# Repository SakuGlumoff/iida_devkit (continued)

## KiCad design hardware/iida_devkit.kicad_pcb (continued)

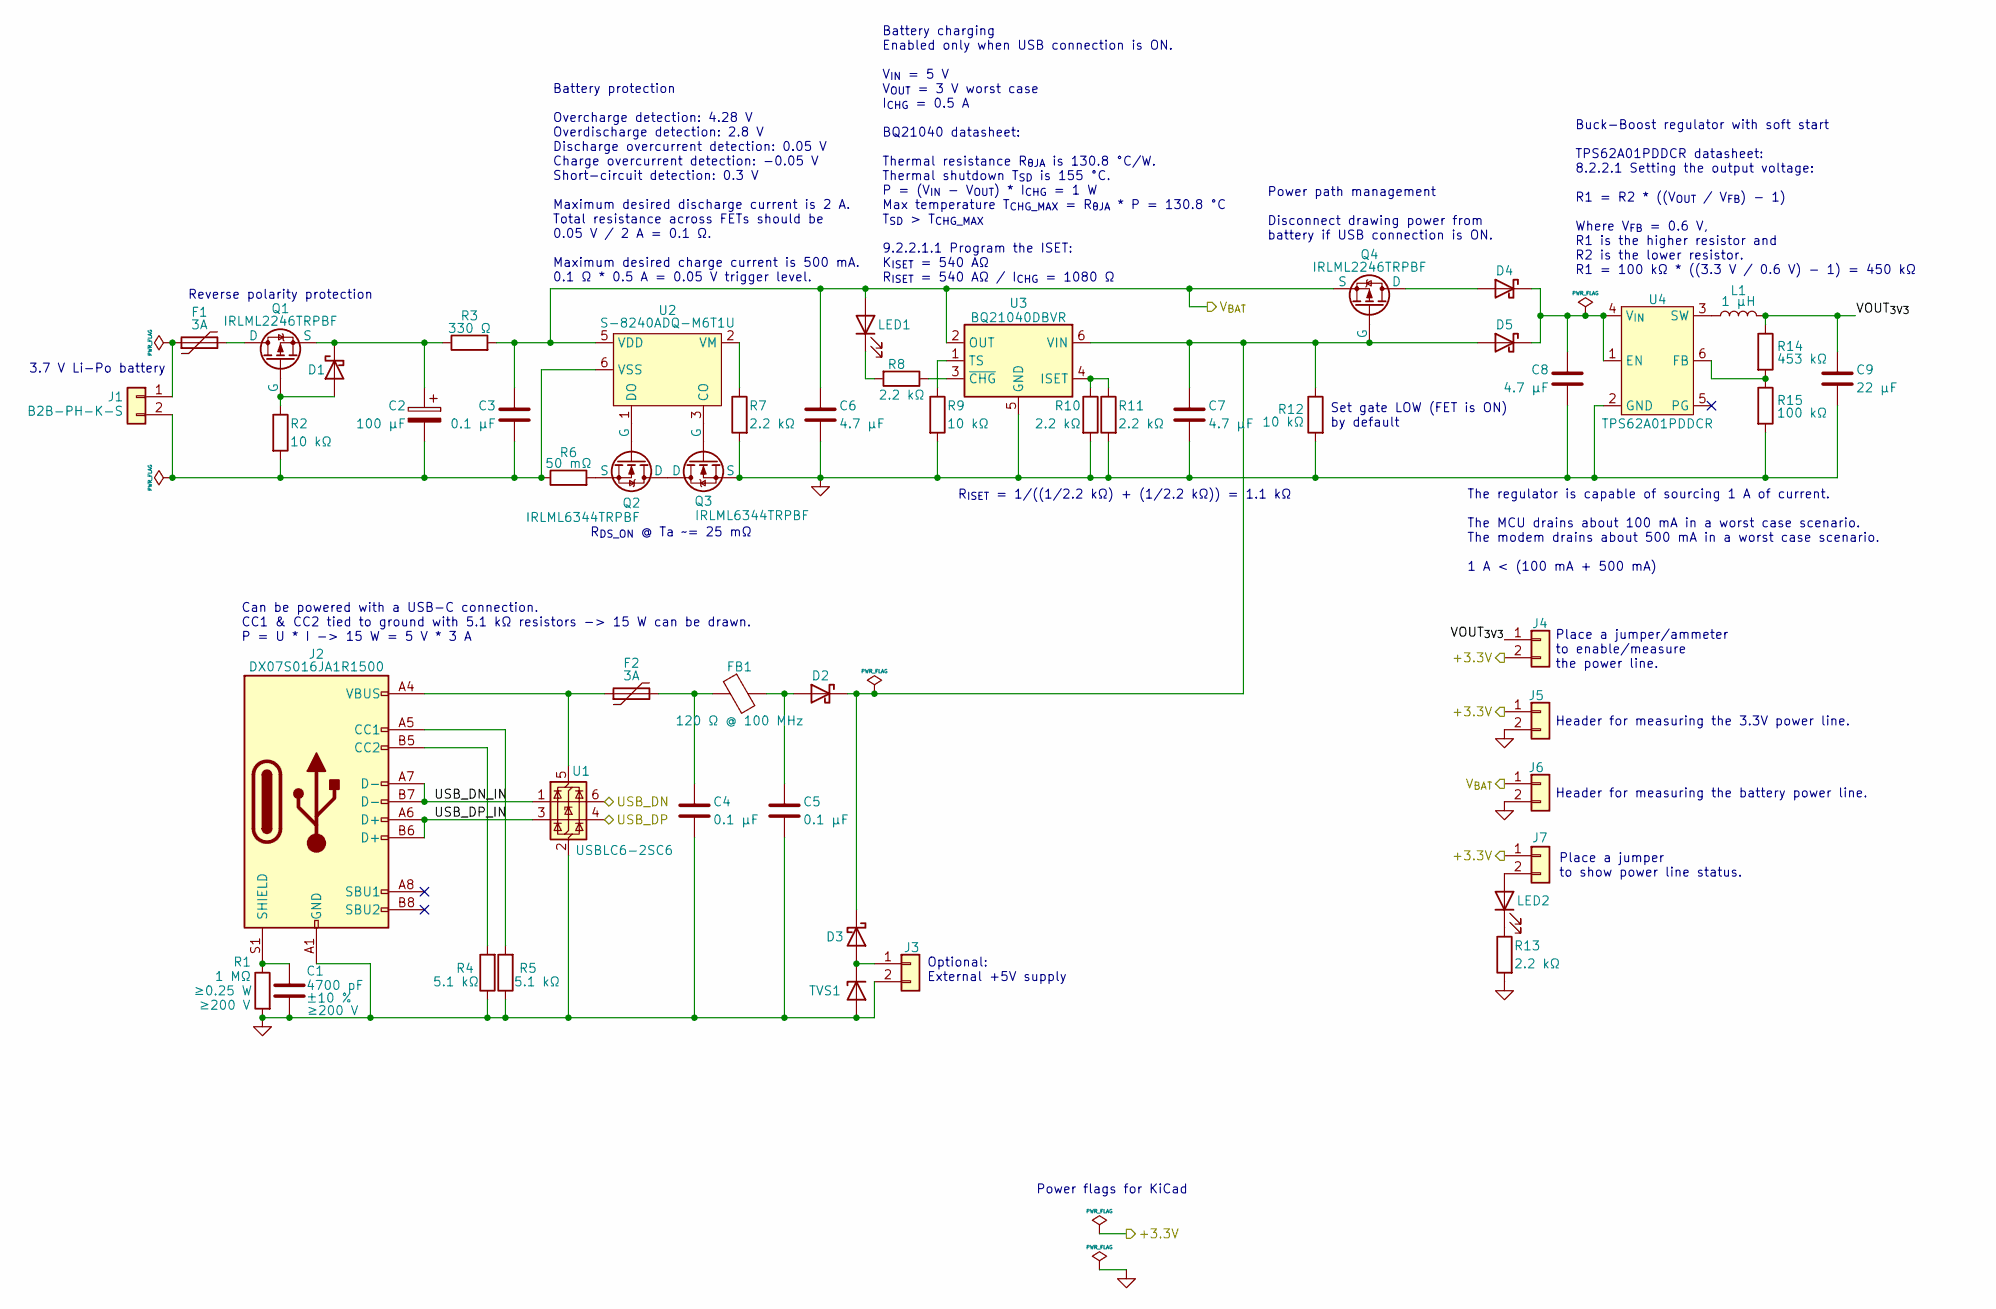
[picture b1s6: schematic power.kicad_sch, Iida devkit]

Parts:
C1: 4700 pF; C_0805_2012Metric_Pad1.18x1.45mm_HandSolder; Voltage rating ≥200 V; Tolerance ±10 %; Manufacturer Part Number 885342207009; Digi-Key Part Number 732-12165-1-ND
C2: 100 µF; CP_Elec_5x5.3; Manufacturer Part Number 865080142007; Digi-Key Part Number 732-8472-1-ND
C3, C4, C5: 0.1 µF; C_0603_1608Metric_Pad1.08x0.95mm_HandSolder; Manufacturer Part Number 885012206071; Digi-Key Part Number 732-7989-1-ND
C6, C7, C8: 4.7 µF; C_0805_2012Metric_Pad1.18x1.45mm_HandSolder; Manufacturer Part Number 885012107013; Digi-Key Part Number 732-7623-1-ND
C9: 22 µF; C_0805_2012Metric_Pad1.18x1.45mm_HandSolder; Manufacturer Part Number 885012107005; Digi-Key Part Number 732-7616-1-ND
D1, D2, D3, D4, D5: BAT60AE6327HTSA1; D_SOD-323_HandSoldering; Manufacturer Part Number BAT60AE6327HTSA1; Digi-Key Part Number BAT60AE6327HTSA1CT-ND
F1, F2: 3A; R_0805_2012Metric_Pad1.20x1.40mm_HandSolder; Manufacturer Part Number PTSLR08056V150; Digi-Key Part Number 283-PTSLR08056V150CT-ND
FB1: 120 Ω @ 100 MHz; R_0603_1608Metric_Pad0.98x0.95mm_HandSolder; Manufacturer Part Number BLM18KG121TN1D; Digi-Key Part Number 490-5254-1-ND
J1: B2B-PH-K-S; JST_PH_B2B-PH-K_1x02_P2.00mm_Vertical; Manufacturer Part Number B2B-PH-K-S; Digi-Key Part Number 455-1704-ND
J2: DX07S016JA1R1500; Manufacturer Part Number DX07S016JA1R1500; Digi-Key Part Number 670-DX07S016JA1R1500CT-ND
J3, J4, J5, J6, J7: PRPC001DAAN-RC; PinHeader_1x02_P2.54mm_Vertical; Manufacturer Part Number PRPC001DAAN-RC; Digi-Key Part Number S2011EC-01-ND
L1: 1 µH; L_1008_2520Metric_Pad1.43x2.20mm_HandSolder; Manufacturer Part Number DFE252012F-1R0M=P2; Digi-Key Part Number 490-13053-1-ND
LED1, LED2: 150141YS73100; LED_PLCC_2835_Handsoldering; Manufacturer Part Number 150141YS73100; Digi-Key Part Number 732-5004-1-ND
Q1, Q4: IRLML2246TRPBF; SC-59_Handsoldering; Manufacturer Part Number IRLML2246TRPBF; Digi-Key Part Number IRLML2246TRPBFCT-ND
Q2, Q3: IRLML6344TRPBF; SC-59_Handsoldering; Manufacturer Part Number IRLML6344TRPBF; Digi-Key Part Number IRLML6344TRPBFCT-ND
R1: 1 MΩ; R_1206_3216Metric_Pad1.30x1.75mm_HandSolder; Power rating ≥0.25 W; Working voltage ≥200 V; Manufacturer Part Number 560112132011; Digi-Key Part Number 732-560112132011CT-ND
R2, R9, R12: 10 kΩ; R_0603_1608Metric_Pad0.98x0.95mm_HandSolder; Manufacturer Part Number 560112116005; Digi-Key Part Number 732-560112116005CT-ND
R3: 330 Ω; R_0603_1608Metric_Pad0.98x0.95mm_HandSolder; Manufacturer Part Number 560112116020; Digi-Key Part Number 732-560112116020CT-ND
R4, R5: 5.1 kΩ; R_0805_2012Metric_Pad1.20x1.40mm_HandSolder; Manufacturer Part Number 560112120019; Digi-Key Part Number 732-560112120019CT-ND
R6: 50 mΩ; R_0603_1608Metric_Pad0.98x0.95mm_HandSolder; Manufacturer Part Number ERJ-3BWFR050V; Digi-Key Part Number P17472CT-ND
R7, R8, R10, R11, R13: 2.2 kΩ; R_0603_1608Metric_Pad0.98x0.95mm_HandSolder; Manufacturer Part Number 560112116098; Digi-Key Part Number 732-560112116098CT-ND
R14: 453 kΩ; R_0603_1608Metric_Pad0.98x0.95mm_HandSolder; Manufacturer Part Number SDR03EZPF4533; Digi-Key Part Number 846-SDR03EZPF4533CT-ND
R15: 100 kΩ; R_0603_1608Metric_Pad0.98x0.95mm_HandSolder; Manufacturer Part Number 560112116004; Digi-Key Part Number 732-560112116004CT-ND
TVS1: SMAJ6.0CA; D_SMA_Handsoldering; Manufacturer Part Number SMAJ6.0CA; Digi-Key Part Number 732-SMAJ6.0CACT-ND
U1: USBLC6-2SC6; SOT-23-6_Handsoldering; Manufacturer Part Number USBLC6-2SC6; Digi-Key Part Number 497-5235-1-ND
U2: S-8240ADQ-M6T1U; SOT-23-6_Handsoldering; Manufacturer Part Number S-8240ADQ-M6T1U; Digi-Key Part Number 1662-S-8240ADQ-M6T1UCT-ND
U3: BQ21040DBVR; SOT-23-6_Handsoldering; Manufacturer Part Number BQ21040DBVR; Digi-Key Part Number 296-47315-1-ND
U4: TPS62A01PDDCR; SOT-23-6_Handsoldering; Manufacturer Part Number TPS62A01PDDCR; Digi-Key Part Number 296-TPS62A01PDDCRCT-ND

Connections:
+3.3V: J4.2, J5.1, J7.1; also elsewhere on the board
+VBAT: C3.1, C6.1, J6.1, LED1.2 (A), Q4.3 (S), R3.2, U2.5 (VDD), U3.2 (OUT); also elsewhere on the board
/MCU/USB_DN: U1.6 (I/O1); also elsewhere on the board
/MCU/USB_DP: U1.4 (I/O2); also elsewhere on the board
/Power/USB_DN_IN: J2.A7 (D-), J2.B7 (D-), U1.1 (I/O1)
/Power/USB_DP_IN: J2.A6 (D+), J2.B6 (D+), U1.3 (I/O2)
/Power/VOUT_{3V3}: C9.1, J4.1, L1.2, R14.1
GND: C1.2, C4.2, C5.2, C6.2, C7.2, C8.2, C9.2, J2.A1 (GND), J2.A12 (GND), J2.B1 (GND), J2.B12 (GND), J3.2, J5.2, J6.2, Q3.3 (S), R1.2, R4.1, R5.1, R7.2, R9.2, R10.2, R11.2, R12.2, R13.2, R15.2, TVS1.2 (A), U1.2 (GND), U3.5 (GND), U4.2 (GND); also elsewhere on the board
unnamed: C4.1, F2.2, FB1.1
unnamed: D1.2 (A), Q1.2 (G), R2.1
unnamed: C2.1, D1.1 (K), Q1.3 (S), R3.1
unnamed: C5.1, D2.2 (A), FB1.2
unnamed: C7.1, D2.1 (K), D3.1 (K), D5.2 (A), Q4.2 (G), R12.1, U3.6 (VIN)
unnamed: D3.2 (A), J3.1, TVS1.1 (K)
unnamed: D4.2 (A), Q4.1 (D)
unnamed: C8.1, D4.1 (K), D5.1 (K), U4.1 (EN), U4.4 (V_{IN})
unnamed: F1.1, J1.1
unnamed: C2.2, C3.2, J1.2, R2.2, R6.1, U2.6 (VSS)
unnamed: J2.A5 (CC1), R5.2
unnamed: J2.B5 (CC2), R4.2
unnamed: C1.1, J2.S1 (SHIELD), R1.1
unnamed: J7.2, LED2.2 (A)
unnamed: LED1.1 (K), R8.2
unnamed: LED2.1 (K), R13.1
unnamed: F1.2, Q1.1 (D)
unnamed: Q2.1 (D), Q3.1 (D)
unnamed: Q2.2 (G), U2.1 (DO)
unnamed: Q2.3 (S), R6.2
unnamed: Q3.2 (G), U2.3 (CO)
unnamed: F2.1, J2.A4 (VBUS), J2.A9 (VBUS), J2.B4 (VBUS), J2.B9 (VBUS), U1.5 (VBUS)
unnamed: R7.1, U2.2 (VM)
unnamed: R10.1, R11.1, U3.4 (ISET)
unnamed: R9.1, U3.1 (TS)
unnamed: R8.1, U3.3 (~CHG)
unnamed: R14.2, R15.1, U4.6 (FB)
unnamed: L1.1, U4.3 (SW)

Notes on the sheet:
R_{ISET} = 1/((1/2.2 kΩ) + (1/2.2 kΩ)) = 1.1 kΩ
Can be powered with a USB-C connection. CC1 & CC2 tied to ground with 5.1 kΩ resistors -> 15 W can be drawn. P = U * I -> 15 W = 5 V * 3 A
R_{DS_ON} @ Ta ~= 25 mΩ
3.7 V Li-Po battery
Reverse polarity protection
Set gate LOW (FET is ON) by default
Buck-Boost regulator with soft start TPS62A01PDDCR datasheet: 8.2.2.1 Setting the output voltage: R1 = R2 * ((V_{OUT} / V_{FB}) - 1) Where V_{FB} = 0.6 V, R1 is the higher resistor and R2 is the lower resistor. R1 = 100 kΩ * ((3.3 V / 0.6 V) - 1) = 450 kΩ
Power path management Disconnect drawing power from battery if USB connection is ON.
Optional: External +5V supply
Power flags for KiCad
Place a jumper to show power line status.
Header for measuring the battery power line.
Battery protection Overcharge detection: 4.28 V Overdischarge detection: 2.8 V Discharge overcurrent detection: 0.05 V Charge overcurrent detection: -0.05 V Short-circuit detection: 0.3 V Maximum desired discharge current is 2 A. Total resistance across FETs should be 0.05 V / 2 A = 0.1 Ω. Maximum 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
Battery charging Enabled only when USB connection is ON. V_{IN} = 5 V V_{OUT} = 3 V worst case I_{CHG} = 0.5 A BQ21040 datasheet: Thermal resistance R_{θJA} is 130.8 °C/W. Thermal shutdown T_{SD} is 155 °C. P = (V_{IN} - V_{OUT}) * I_{CHG} = 1 W Max temperature T_{CHG_MAX} = R_{θJA} * P = 130.8 °C 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
Place a jumper/ammeter to enable/measure the power line.
Header for measuring the 3.3V power line.
The regulator is capable of sourcing 1 A of current. The MCU drains about 100 mA in a worst case scenario. The modem drains about 500 mA in a worst case scenario. 1 A < (100 mA + 500 mA)

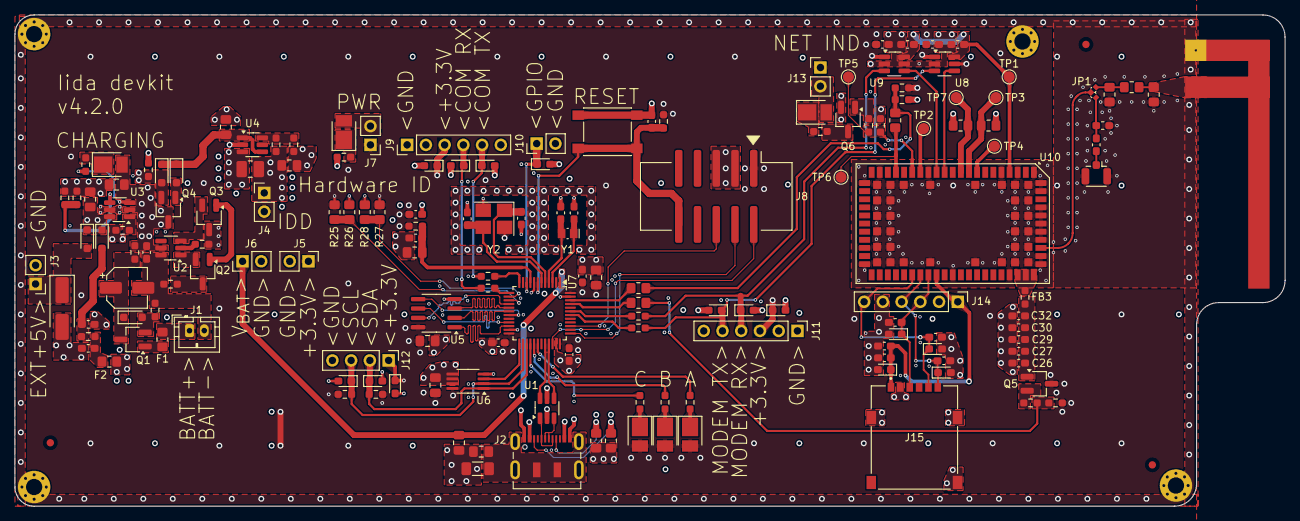
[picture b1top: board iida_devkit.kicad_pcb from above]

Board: 4 copper layers, 172.2 x 66.6 mm, 167 parts (0 on the bottom side), 100 nets.

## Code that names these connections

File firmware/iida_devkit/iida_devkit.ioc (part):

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Mcu.Name=STM32L552C(C-E)Tx
Mcu.Package=LQFP48
Mcu.UserName=STM32L552CETx
PA11.GPIOParameters=GPIO_Label
PA11.GPIO_Label=USB_DN
PA11.Mode=Device
PA11.Signal=USB_DM
PA12.Mode=Device
PA12.Signal=USB_DP
PA13\ (JTMS/SWDIO).GPIOParameters=GPIO_Label
PA13\ (JTMS/SWDIO).GPIO_Label=SWDIO
PA13\ (JTMS/SWDIO).Mode=Trace_Asynchronous_SW
PA13\ (JTMS/SWDIO).Signal=DEBUG_JTMS-SWDIO
PA14\ (JTCK/SWCLK).GPIOParameters=GPIO_Label
PA14\ (JTCK/SWCLK).GPIO_Label=SWCLK
PA14\ (JTCK/SWCLK).Mode=Trace_Asynchronous_SW
PA14\ (JTCK/SWCLK).Signal=DEBUG_JTCK-SWCLK
PA2.GPIOParameters=GPIO_Label
PA2.GPIO_Label=COM_UART_TX
PA2.Mode=Asynchronous
PA2.Signal=USART2_TX
PA3.GPIOParameters=GPIO_Label
PA3.GPIO_Label=COM_UART_RX
PA3.Mode=Asynchronous
PA3.Signal=USART2_RX
PA4.GPIOParameters=GPIO_Label
PA4.GPIO_Label=HWID_1
PA4.Signal=GPIO_Input
PA5.GPIOParameters=GPIO_Label
PA5.GPIO_Label=HWID_2
PA5.Signal=GPIO_Input
PA6.GPIOParameters=GPIO_Label
PA6.GPIO_Label=EXT_FLASH_IO3
PA6.Mode=quad_mode
PA6.Signal=OCTOSPI1_IO3
PA7.GPIOParameters=GPIO_Label
PA7.GPIO_Label=EXT_FLASH_IO2
PA7.Mode=quad_mode
PA7.Signal=OCTOSPI1_IO2
PA8.GPIOParameters=GPIO_Label
PA8.GPIO_Label=LED_B
PA8.Signal=GPIO_Output
PA9.GPIOParameters=GPIO_Label
PA9.GPIO_Label=LED_A
PA9.Signal=GPIO_Output
PB0.GPIOParameters=GPIO_Label
PB0.GPIO_Label=EXT_FLASH_IO1
PB0.Mode=quad_mode
PB0.Signal=OCTOSPI1_IO1
PB1.GPIOParameters=GPIO_Label
PB1.GPIO_Label=EXT_FLASH_IO0
PB1.Mode=quad_mode
PB1.Signal=OCTOSPI1_IO0
PB10.GPIOParameters=GPIO_Label
PB10.GPIO_Label=EXT_FLASH_CLK
PB10.Mode=quad_mode
PB10.Signal=OCTOSPI1_CLK
PB11.GPIOParameters=GPIO_Label
PB11.GPIO_Label=EXT_FLASH_NCS
PB11.Mode=quad_mode
PB11.Signal=OCTOSPI1_NCS
PB12.GPIOParameters=GPIO_Label
PB12.GPIO_Label=TEMP_ALERT
PB12.Signal=GPXTI12
PB13.GPIOParameters=GPIO_Label
PB13.GPIO_Label=I2C_SCL
PB13.Mode=I2C
PB13.Signal=I2C2_SCL
PB14.GPIOParameters=GPIO_Label
PB14.GPIO_Label=I2C_SDA
PB14.Mode=I2C
PB14.Signal=I2C2_SDA
PB15.GPIOParameters=GPIO_Label
PB15.GPIO_Label=LED_C
PB15.Signal=GPIO_Output
PB3\ (JTDO/TRACESWO).GPIOParameters=GPIO_Label
PB3\ (JTDO/TRACESWO).GPIO_Label=SWO
PB3\ (JTDO/TRACESWO).Mode=Trace_Asynchronous_SW
PB3\ (JTDO/TRACESWO).Signal=DEBUG_JTDO-SWO
PB6.GPIOParameters=GPIO_Label
PB6.GPIO_Label=MODEM_TX
PB6.Mode=Asynchronous
PB6.Signal=USART1_TX
PB7.GPIOParameters=GPIO_Label
PB7.GPIO_Label=MODEM_RX
PB7.Mode=Asynchronous
PB7.Signal=USART1_RX
PB8.GPIOParameters=GPIO_Label
PB8.GPIO_Label=MODEM_PWR_EN_N
PB8.Signal=GPIO_Output
PB9.GPIOParameters=GPIO_Label
PB9.GPIO_Label=MODEM_RESET_N
PB9.Signal=GPIO_Output
PC14-OSC32_IN\ (PC14).GPIOParameters=GPIO_Label
PC14-OSC32_IN\ (PC14).GPIO_Label=LSE_IN
PC14-OSC32_IN\ (PC14).Mode=LSE-External-Oscillator
PC14-OSC32_IN\ (PC14).Signal=RCC_OSC32_IN
PC15-OSC32_OUT\ (PC15).GPIOParameters=GPIO_Label
PC15-OSC32_OUT\ (PC15).GPIO_Label=LSE_OUT
PC15-OSC32_OUT\ (PC15).Mode=LSE-External-Oscillator
PC15-OSC32_OUT\ (PC15).Signal=RCC_OSC32_OUT
PH0-OSC_IN\ (PH0).GPIOParameters=GPIO_Label
PH0-OSC_IN\ (PH0).GPIO_Label=HSE_IN
PH0-OSC_IN\ (PH0).Mode=HSE-External-Oscillator
PH0-OSC_IN\ (PH0).Signal=RCC_OSC_IN
PH1-OSC_OUT\ (PH1).GPIOParameters=GPIO_Label
PH1-OSC_OUT\ (PH1).GPIO_Label=HSE_OUT
PH1-OSC_OUT\ (PH1).Mode=HSE-External-Oscillator
PH1-OSC_OUT\ (PH1).Signal=RCC_OSC_OUT
RCC.HSE_VALUE=16000000
RCC.SYSCLKFreq_VALUE=100000000
RCC.SYSCLKSource=RCC_SYSCLKSOURCE_PLLCLK
board=custom

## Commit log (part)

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2024-06-08 Initial commit with cleaned up history
2024-06-09 Add stubs to fix builds
2024-06-09 Start working on GPIO
2024-06-09 Add GPIO support
2024-06-09 Start system init support
2024-06-15 test
2024-06-15 Fix CI build
2024-06-30 Replace Jenkins with GitHub actions
2024-06-30 Update README files
2024-07-01 Develop bootloader system further
2024-07-01 Build all targets by default in VS Code
2024-07-01 Add SeggerRTT to bootloader
2024-07-01 Fix bootloader main codestyle
2024-07-01 Move PTSW to firmware
2024-07-01 Finish PTSW QSPI test
2024-07-01 Add assignment operator support for GPIO
    Add support to the GPIO drivers to allow doing the following:
    ```
    Gpio pin(PORT_A, PIN_1);
    pin = 1;
    pin = 0;
    pin = false;
2024-07-01 Add assignment operator support for GPIO (#6)
    Add support to the GPIO drivers to allow doing the following:
    ```
    Gpio pin(PORT_A, PIN_1);
    pin = 1;
    pin = 0;
    pin = false;
2024-07-04 Fix stuff based on testing
2024-07-04 Apply fixes to PTSW based on testing
2024-07-04 Fix bootloader based on testing
2024-07-06 Fix UART based on testing
2024-07-06 Refactor to include Segger RTT
2024-07-06 Bugfixes and YModem support
    - Increase stack size to fix crash when using Segger RTT stuff
    - Start adding YModem support for bootloader
2024-07-06 Finish up XModem support
2024-07-06 Remove unnecessary debug prints
2024-07-06 YModem -> XModem
2024-07-06 Add 1K packet support
2024-07-10 Simplify UARTs
2024-07-10 Fix RTT crash
2024-07-10 Comment UART stuff
2024-07-10 Fix XMODEM receive packet return type
2024-07-10 Generate a binary from application hex with header
2024-07-10 Start working on flash support
2024-07-10 Develop flash support further, erase doesn't work
2024-07-11 Fix issues with Flash and use it for self tests
2024-07-11 Write application image sent via XMODEM to flash
2024-07-11 Ease debugging BL and App
2024-07-12 Rework app header implementation
2024-07-12 Support jump to application
2024-07-12 Refactor memorymap and its usage
2024-07-12 Add launch configuration to only debug the App
2024-07-12 Update FW verification workflow
2024-07-12 Update CRC calculation in firmware
2024-07-12 Refactor app header usage
2024-07-16 Start adding I2C support
2024-07-25 Clean up the build
2024-07-25 Add VSCode extension recommendations
2024-08-18 Fix application code alignment issue
2024-08-19 Clean up flash driver
    Closes #3
2024-08-19 Update kicad libraries
2024-08-27 Refine formatting
2024-08-27 GNU_ARM_PATH -> ARM_GNU_PATH
2024-08-29 Add devcontainer and Dockerfile
2024-08-29 Set FW verification to use docker
2024-08-29 Add docker support and use it for CI (#7)
    * Add devcontainer and Dockerfile
    * Set FW verification to use docker
2024-08-30 Add metadata to bl+app
    Closes #5
2024-08-30 Add metadata to bootloader and application (#8)
    Closes #5
2024-08-30 Print metadata at bl and app boot
2024-09-01 Remove PTSW, update DebugPrint-GCC, add FreeRTOS
2024-09-01 Remove PTSW, update DebugPrint-GCC, add FreeRTOS (#9)
2024-09-06 Start working on hw v4.0.0
2024-09-07 HW: Continue developing
2024-09-08 HW: Develop further
2024-09-09 Update 4 layer stackup project rules
2024-09-09 HW: Layout power section
2024-09-09 HW: Initial MCU layout
2024-09-09 HW: Layout SIM section
2024-09-09 HW: Layout modem
2024-09-09 HW: Finish laying out sections
2024-09-10 HW: Make sections more compact
2024-09-10 HW: Rework power section
2024-09-10 HW: Replace SMA with U.FL
2024-09-10 HW: Ready for routing
2024-09-10 HW: Route power
2024-09-10 HW: Initial layout and routing done
2024-09-10 HW: Stitch layers together
2024-09-11 HW: Fix via placement
2024-09-11 HW: Cleanup
2024-09-11 HW: Add teardrops
2024-09-11 HW: Place components on top layer only
2024-09-15 WIP: Add Modem support
2024-09-20 HW: Update schematic
2024-09-20 HW: Start PCB over with new stackup
2024-09-20 HW: Add PCB antenna option
2024-09-20 HW: Add layout guidelines/reminders to schematic
2024-09-20 HW: Cleanup schematic
2024-09-20 HW: Layout power
2024-09-21 HW: Fix PCB antenna
2024-09-21 HW: Add series termination to UART lines
2024-09-21 HW: Layout antenna
2024-09-21 HW: Layout SIM
2024-09-21 HW: Layout Modem and SIM
2024-09-21 HW: Route MCU
2024-09-21 HW: Finish sections
2024-09-21 HW: Connect signals
2024-09-21 HW: Finish layout
2024-09-21 HW: Stitch grounds together
2024-09-21 HW: Fix HWID R15
2024-09-22 HW: Change USB connector, add TVS to headers, fix layout
2024-09-22 HW: Cleanup layout
2024-09-22 HW: Update date on sheets
2024-09-22 HW: Update 0hm choice
2024-09-22 HW: Update BOM
2024-09-22 HW: Fix BOM
2024-09-22 HW: TC2030 -> TC2050
2024-09-22 HW: BOM consolidate
2024-09-22 HW: Replace chinese NPN BJT
2024-09-25 HW: Connect +BATT to MCU
2024-09-26 HW: Improve thermals, silkscreen and schematic
2024-09-26 HW: Update components
2024-09-28 HW: Update VBAT, schema and layout
2024-09-28 HW: Start adding Li-Po support
2024-10-05 HW: Fix 5.1K USB resistors
2024-10-05 HW: Replace STM QFN with QFP
2024-10-05 HW: Replace TC2050 wiht 10-pin connector
2024-10-05 HW: Update components to be hand solderable
2024-10-05 HW: Update components, change footprints to handsolder versions, finish power
2024-10-06 HW: Add fuses to USB and battery
2024-10-06 HW: Add formula for FB resistors of regulator
2024-10-06 HW: Add battery protection
2024-10-06 HW: Resize modem power fet gate resistor
2024-10-06 HW: Replace 0402 with 0603 or bigger
2024-10-06 HW: Start layout all over again
2024-10-06 HW: Fix 3D models for components
2024-10-06 HW: Layout antenna section
2024-10-06 HW: Layout modem and SIM together
2024-10-07 HW: Layout MCU section
2024-10-08 HW: Refine modem layout
2024-10-08 HW: Route sections together
2024-10-09 HW: Connect nets and fill layers
2024-10-09 HW: Fix programming header and layout
2024-10-09 HW: Refactor layout
2024-10-10 HW: Add bulk cap to VBAT
2024-10-10 HW: Document current consumption to power sheet
2024-10-10 HW: Color code nets
2024-10-10 HW: Use teardrops
2024-10-10 HW: Fix teardrops
2024-10-10 HW: Refine schema
2024-10-11 HW: Add project description to main schema sheet
2024-10-11 HW: Replace USB-C connector
2024-10-11 HW: Fix components
2024-10-11 HW: Refine schema text
2024-10-12 HW: Refine schema and layout
2024-10-12 HW: Refine schema and layout based on review
2024-10-12 HW: Improve thermals
2024-10-13 HW: Fix antenna selection stub
2024-10-13 HW: Fix power dissipation calculation in power sheet
2024-10-13 HW: Improve external antenna placement
2024-10-13 HW: Improve power delivery
2024-10-14 HW: Fix component assignments
2024-10-14 HW: Add via fence and stitch planes
2024-10-15 HW: Improve layout
2024-10-15 HW: Fix C1 footprint
2024-10-15 HW: Fix footprints
2024-10-15 HW: Fix layout
2024-10-15 HW: Export BOM to manufacturing dir
